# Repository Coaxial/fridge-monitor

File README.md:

fridge-monitor
==============

Monitors fridge + freezer temps

I wrote this Arduino sketch to monitor the temperature of the freezer and the fridge. It shows the current temps on a 4*20 HD4470 LCD along with the trend for each temperature sensor.

It has an alarm for when the temps are too high or too low.

Current issues:
  - Can't get reliable readings from the temperature sensors
  - Uses way too much energy to be run on batteries

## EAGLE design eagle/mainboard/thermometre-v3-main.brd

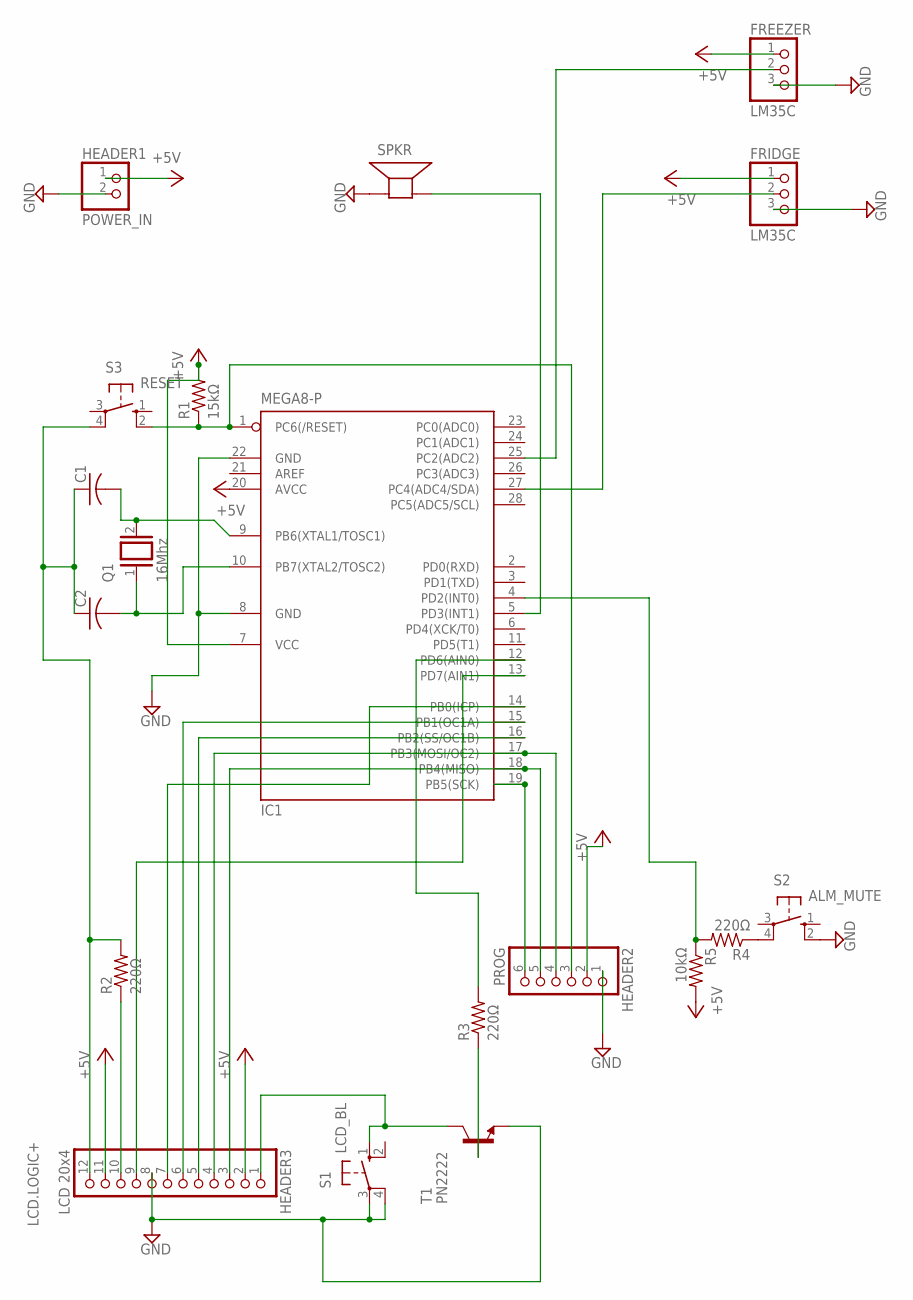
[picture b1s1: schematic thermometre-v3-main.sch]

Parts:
C1, C2: C-USC0805; C0805
FREEZER: LM35C; 1X03
FRIDGE: LM35C; 1X03
HEADER1: POWER_IN; 1X02
HEADER2: PROG; 1X06
HEADER3: LCD 20x4; 1X12
IC1: MEGA8-P; DIL28-3
Q1: 16Mhz; QS
R1: 15kΩ; R0805
R2, R3, R4: 220Ω; R0805
R5: 10kΩ; R0805
S1: LCD_BL; B3F-10XX
S2: ALM_MUTE; B3F-10XX
S3: RESET; B3F-10XX
SPKR: SPEAKER/AL60P; AL60P
T1: PN2222; TO92-CBE

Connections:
+5V: FREEZER.1, FRIDGE.1, HEADER1.1, HEADER2.2, HEADER3.2, IC1.7 (VCC), IC1.20 (AVCC), R1.2, R5.2
GND: FREEZER.3, FRIDGE.3, HEADER1.2, HEADER2.1, HEADER3.8, IC1.8 (GND), IC1.22 (GND), S1.3, S1.4 (P1), S2.2 (S1), SPKR.1 (+), T1.E
LCD.BL+: HEADER2.5, HEADER3.3, IC1.18 (PB4(MISO))
LCD.BL-: HEADER3.1, S1.1 (S), T1.C
LCD.CONTRAST: HEADER3.10, R2.1
LCD.LOGIC+: C1.1, C2.1, HEADER3.12, R2.2, S3.4 (P1)
LCD.LOGIC-: HEADER3.11
unnamed: C1.2, IC1.9 (PB6(XTAL1/TOSC1)), Q1.2
unnamed: C2.2, IC1.10 (PB7(XTAL2/TOSC2)), Q1.1
unnamed: HEADER2.3, IC1.1 (PC6(/RESET)), R1.1, S3.2 (S1)
unnamed: HEADER2.6, IC1.19 (PB5(SCK))
unnamed: HEADER2.4, HEADER3.4, IC1.17 (PB3(MOSI/OC2))
unnamed: R4.1, S2.4 (P1)
unnamed: HEADER3.7, IC1.14 (PB0(ICP))
unnamed: HEADER3.9, IC1.13 (PD7(AIN1))
unnamed: HEADER3.6, IC1.15 (PB1(OC1A))
unnamed: HEADER3.5, IC1.16 (PB2(SS/OC1B))
unnamed: IC1.12 (PD6(AIN0)), R3.2
unnamed: R3.1, T1.B
unnamed: FRIDGE.2, IC1.27 (PC4(ADC4/SDA))
unnamed: IC1.5 (PD3(INT1)), SPKR.2 (-)
unnamed: IC1.4 (PD2(INT0)), R4.2, R5.1
unnamed: FREEZER.2, IC1.25 (PC2(ADC2))

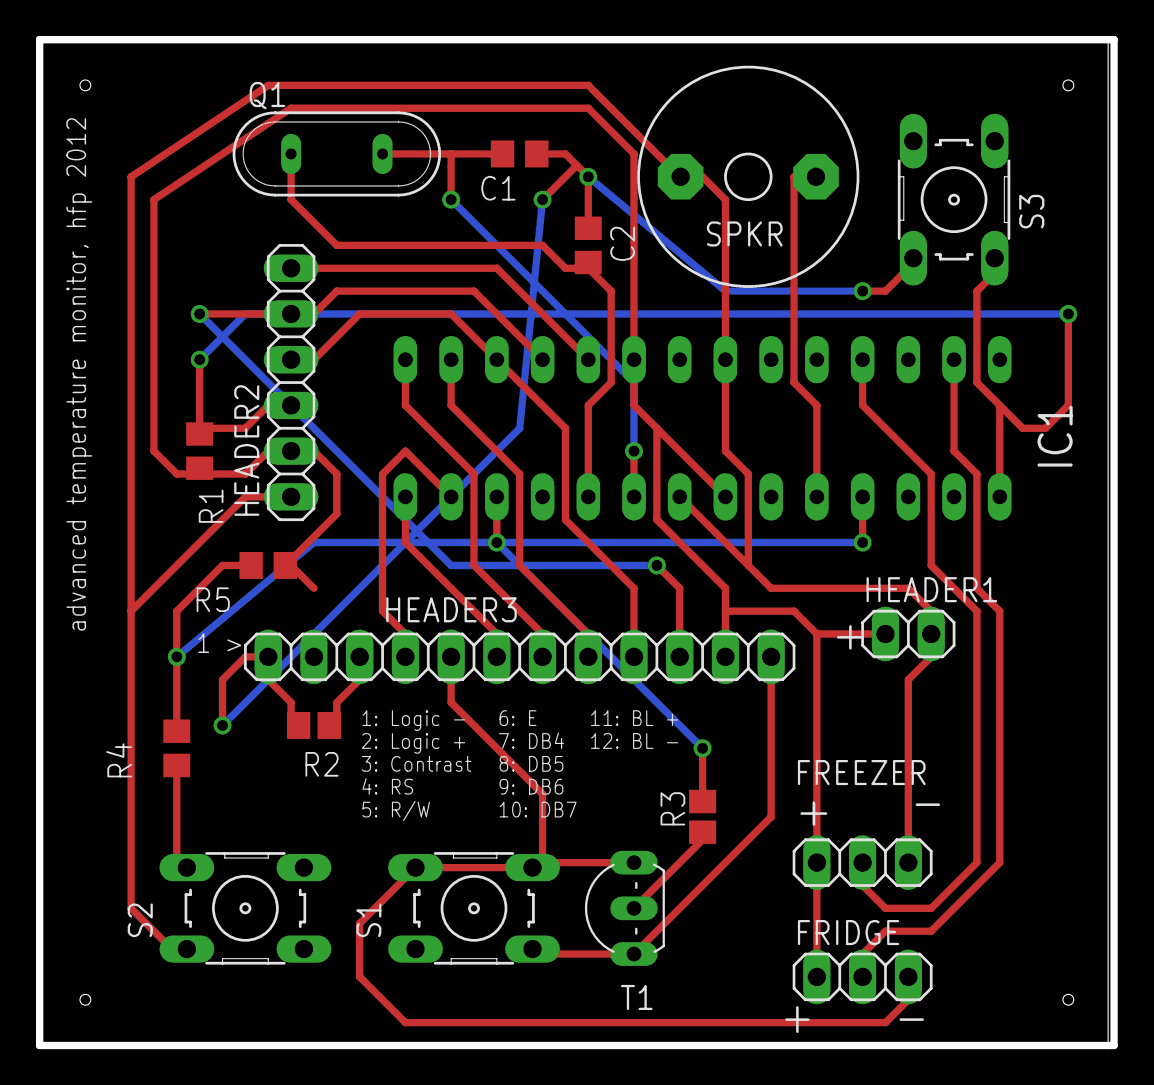
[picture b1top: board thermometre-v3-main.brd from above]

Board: 2 copper layers, 59.7 x 55.9 mm, 19 parts (1 on the bottom side), 22 nets.

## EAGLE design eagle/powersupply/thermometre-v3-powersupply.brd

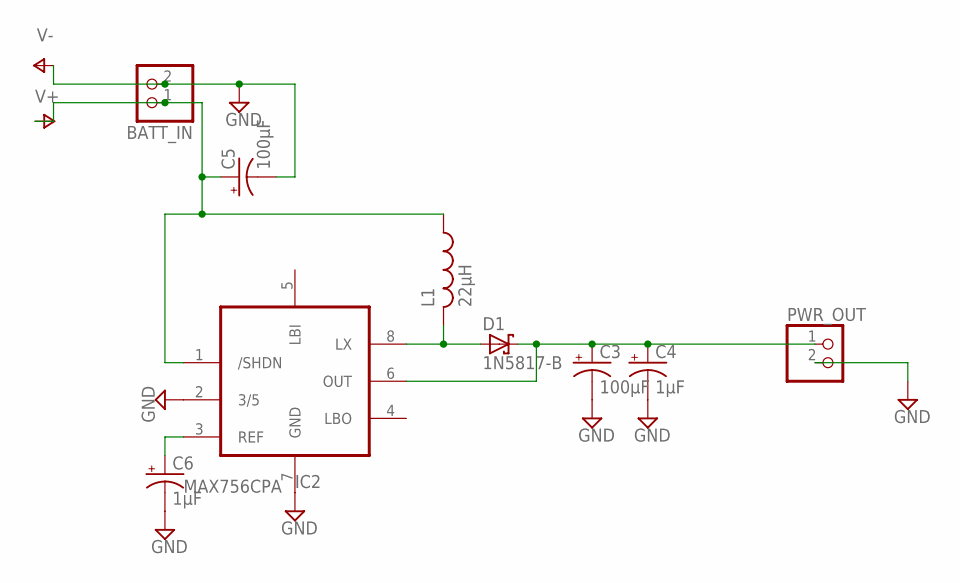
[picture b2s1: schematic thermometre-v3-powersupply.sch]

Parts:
BATT_IN: PINHD-1X2; 1X02
C3: 100µF; E2-5
C4: 1µF; E2-5
C5: 100µF; E2,5-5
C6: 1µF; E2,5-5
D1: 1N5817-B; DO41-7.6
IC2: MAX756CPA; DIL08
L1: 22µH; 0204/7
PWR_OUT: PINHD-1X2; 1X02

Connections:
+5V: C3.+, C4.+, D1.C, IC2.6 (OUT), PWR_OUT.1
GND: BATT_IN.2, C3.-, C4.-, C5.-, C6.-, IC2.2 (3/5), IC2.7 (GND), PWR_OUT.2
unnamed: D1.A, IC2.8 (LX), L1.2
unnamed: C6.+, IC2.3 (REF)
V+: BATT_IN.1, C5.+, IC2.1 (/SHDN), L1.1

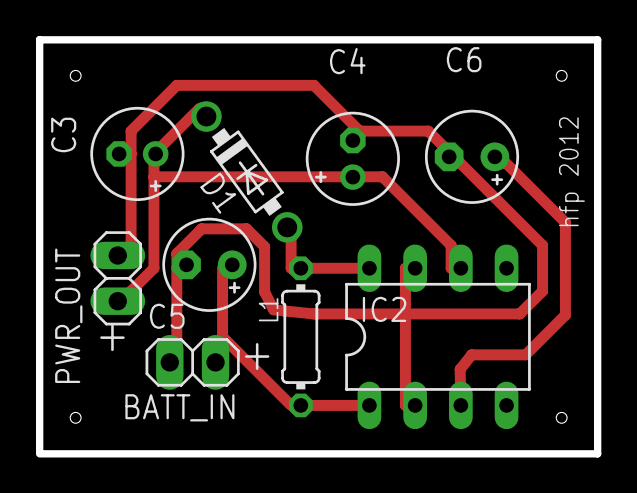
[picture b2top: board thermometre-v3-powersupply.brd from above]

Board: 2 copper layers, 31.0 x 23.0 mm, 9 parts (0 on the bottom side), 5 nets.

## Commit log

2014-02-28 removed .DS_Store
